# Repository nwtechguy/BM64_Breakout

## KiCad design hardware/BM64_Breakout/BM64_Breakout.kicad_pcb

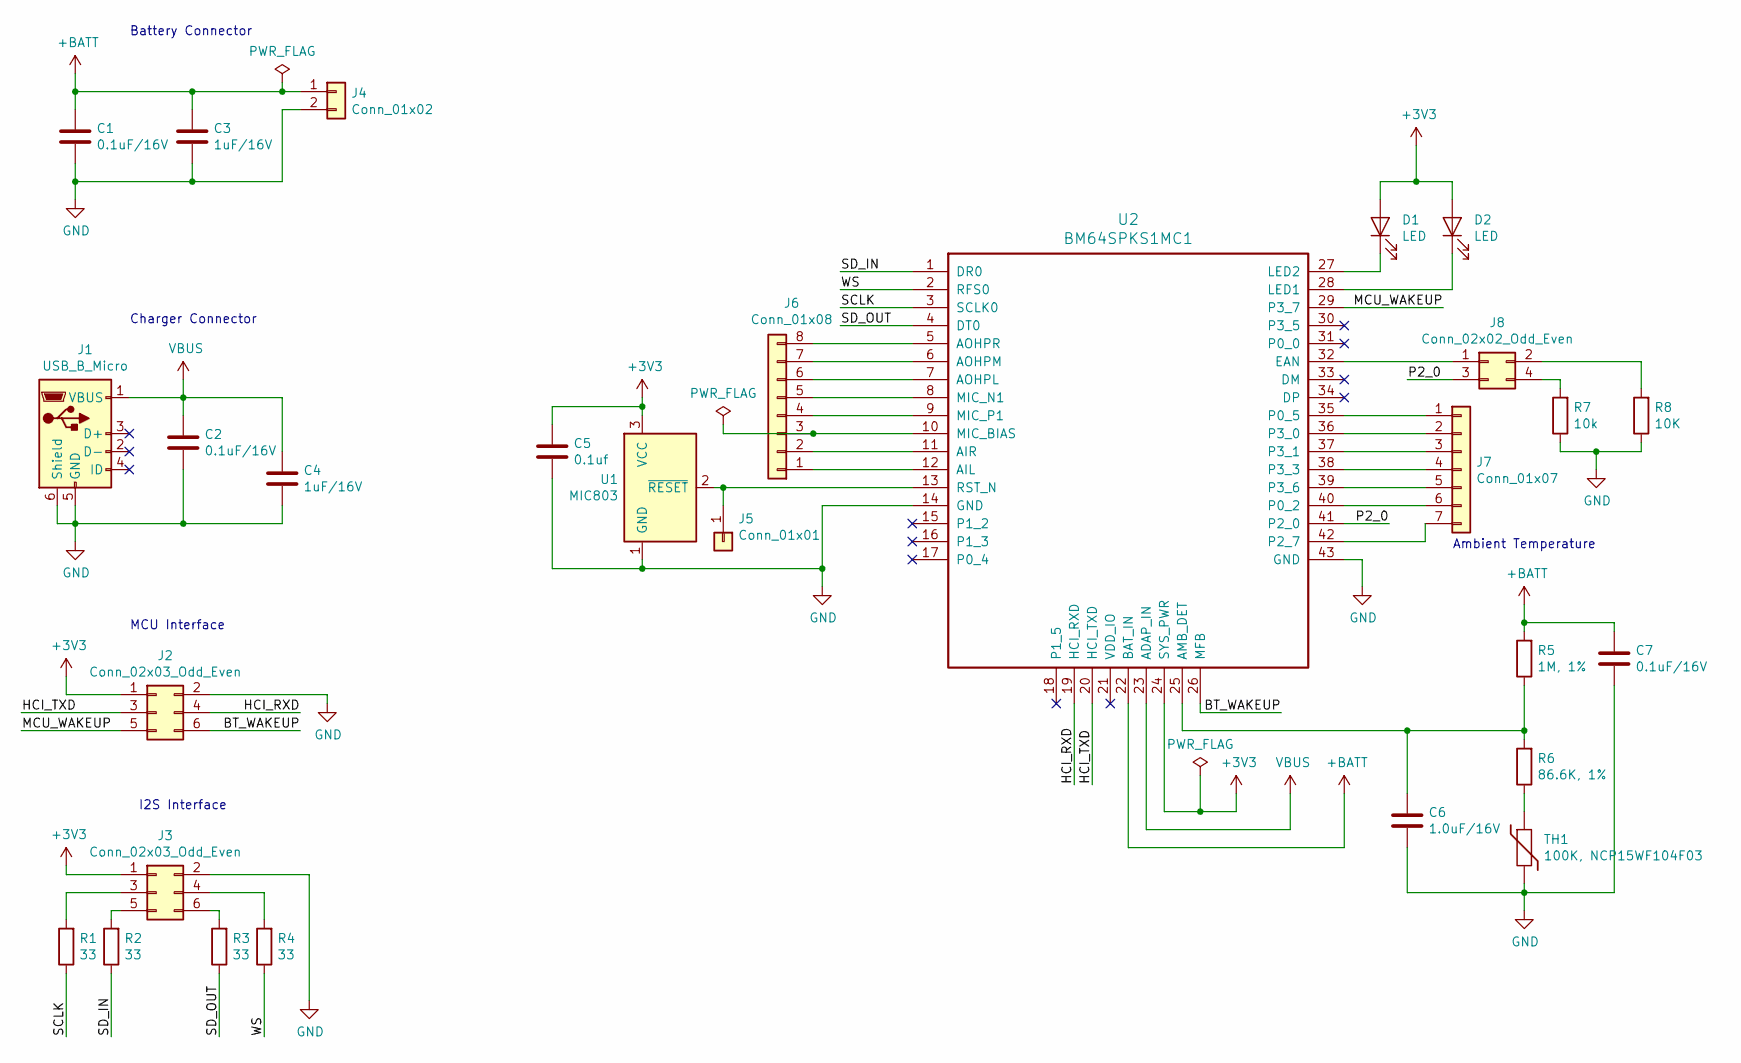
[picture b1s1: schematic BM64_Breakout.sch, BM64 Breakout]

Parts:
C1, C2, C7: 0.1uF/16V; C_0603_1608Metric
C3, C4: 1uF/16V; C_0603_1608Metric
C5: 0.1uf; C_0603_1608Metric
C6: 1.0uF/16V; C_0603_1608Metric
D1, D2: LED; D_0603_1608Metric
J1: USB_B_Micro; USB_Micro-B_Amphenol_10103594-0001LF_Horizontal
J2, J3: Conn_02x03_Odd_Even; PinHeader_2x03_P2.54mm_Vertical
J4: Conn_01x02; PinHeader_1x02_P2.54mm_Vertical
J5: Conn_01x01; PinHeader_1x01_P2.54mm_Vertical
J6: Conn_01x08; PinHeader_1x08_P2.54mm_Vertical
J7: Conn_01x07; PinHeader_1x07_P2.54mm_Vertical
J8: Conn_02x02_Odd_Even; PinHeader_2x02_P2.54mm_Vertical
R1, R2, R3, R4: 33; R_0603_1608Metric
R5: 1M, 1%; R_0603_1608Metric
R6: 86.6K, 1%; R_0603_1608Metric
R7: 10k; R_0603_1608Metric
R8: 10K; R_0603_1608Metric
TH1: 100K, NCP15WF104F03; R_0402_1005Metric
U1: MIC803; SOT-323_SC-70
U2: BM64SPKS1MC1; BM64_Module

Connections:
+3V3: C5.1, D1.2 (A), D2.2 (A), J2.1, J3.1, U1.3 (VCC), U2.24 (SYS_PWR)
+BATT: C1.1, C3.1, C7.1, J4.1, R5.2, U2.22 (BAT_IN)
/BT_WAKEUP: J2.6, U2.26 (MFB)
/HCI_RXD: J2.4, U2.19 (HCI_RXD)
/HCI_TXD: J2.3, U2.20 (HCI_TXD)
/MCU_WAKEUP: J2.5, U2.29 (P3_7)
/P2_0: J8.3, U2.41 (P2_0)
/SCLK: R1.1, U2.3 (SCLK0)
/SD_IN: R2.1, U2.1 (DR0)
/SD_OUT: R3.1, U2.4 (DT0)
/WS: R4.1, U2.2 (RFS0)
GND: C1.2, C2.2, C3.2, C4.2, C5.2, C6.2, C7.2, J1.5 (GND), J1.6 (Shield), J2.2, J3.2, J4.2, R7.1, R8.1, TH1.2, U1.1 (GND), U2.14 (GND), U2.43 (GND)
unnamed: C6.1, R5.1, R6.2, U2.25 (AMB_DET)
unnamed: D1.1 (K), U2.27 (LED2)
unnamed: D2.1 (K), U2.28 (LED1)
unnamed: J3.3, R1.2
unnamed: J3.4, R4.2
unnamed: J3.5, R2.2
unnamed: J3.6, R3.2
unnamed: J5.1, U1.2 (~RESET~), U2.13 (RST_N)
unnamed: J6.1, U2.12 (AIL)
unnamed: J6.2, U2.11 (AIR)
unnamed: J6.3, U2.10 (MIC_BIAS)
unnamed: J6.4, U2.9 (MIC_P1)
unnamed: J6.5, U2.8 (MIC_N1)
unnamed: J6.6, U2.7 (AOHPL)
unnamed: J6.7, U2.6 (AOHPM)
unnamed: J6.8, U2.5 (AOHPR)
unnamed: J7.1, U2.35 (P0_5)
unnamed: J7.2, U2.36 (P3_0)
unnamed: J7.3, U2.37 (P3_1)
unnamed: J7.4, U2.38 (P3_3)
unnamed: J7.5, U2.39 (P3_6)
unnamed: J7.6, U2.40 (P0_2)
unnamed: J7.7, U2.42 (P2_7)
unnamed: J8.1, U2.32 (EAN)
unnamed: J8.2, R8.2
unnamed: J8.4, R7.2
unnamed: R6.1, TH1.1
VBUS: C2.1, C4.1, J1.1 (VBUS), U2.23 (ADAP_IN)

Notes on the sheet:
Battery Connector
Charger Connector
MCU Interface
I2S Interface
Ambient Temperature

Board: 2 copper layers, 28 parts (0 on the bottom side), 40 nets, no tracks yet.

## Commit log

2018-11-01 Added schematic for Breakout board
2020-06-08 Updated from Mac

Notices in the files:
hardware/BM64_Breakout/BM64_Breakout.sch:
Copyright © 2018 NW Tech Guy LLC
License: CERN OHL v1.2
